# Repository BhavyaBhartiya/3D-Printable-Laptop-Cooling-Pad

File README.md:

# 3D Printable Laptop Cooling Pad

This is an open source laptop cooling pad designed to force air into the laptop like the Ilano V10 Cooling Pad. It uses 2 Arctic P12 Pro fans set in back portion of the cooling pad instead of th emiddle as most laptops have ducts at the back and not in the middle. It also uses a custom RP2040 based board to control the fan speed on the basis of the temperature of the CPU if in automatic mode or to set the fans to a constant speed if in manual mode. It requires a seperate 12v Power Input to run it without increasing load on the laptop by using the laptop to supply power to it. If it is to be  used in automatic mode then it should be connected to the laptop by a seperate cable so that the laptop can provide it with the CPU temperatures.

## Instructons for Using and Assembly

1. Attach the PCB to the area enclosed by 3 thin walls in between the fan. The PCB should slip in and sit snugly in the enclosure as it has been built to the exact dimensions for the pcb.

2. If you plan on using only manual mode then connect the 6 pin usb c receptacle to an external 12V Power Supply. The 6 pin USB C receptacle is the one on the right of the RP2040 chip.

3. If you wish to use automatic mode as well then attach a cable from any port of the computer to the 14 pin usb c receptacle present straight ahead of the RP2040 chip.

4. The OLED scrren will show current mode, fan speed and if any fan is facing any errors. If it is in automatic mode then it will also show the CPU temperature which will be updated once every 5 seconds.

5. You can use the Increase/ Decrease Buttons to increase or decrease the RPM of the fan by 500 in Manual Mode.

6. You can use the Mode Button to toggle the Mode of the Cooling Pad.

## Schematic

## PCB

## 3D-Design

## External Circuit

## BOM
| Designator                                            | Footprint                                       | Quantity | Value                         | LCSC Part # | Unit Price USD | Design Qty Cost USD | Link                                                                            |
|-------------------------------------------------------|-------------------------------------------------|----------|-------------------------------|-------------|----------------|---------------------|---------------------------------------------------------------------------------|
| C1, C19, C20                                          | 603                                             | 3        | 10uF                          | C96446      | 0.0557         | 0.1671              | https://www.lcsc.com/product-detail/C96446.html                                 |
| C2                                                    | 603                                             | 1        | 22uF                          | C2762594    | 0.1021         | 0.1021              | https://www.lcsc.com/product-detail/C2762594.html                               |
| C21, C24                                              | 402                                             | 2        | 1uF                           | C52923      | 0.0122         | 0.0244              | https://www.lcsc.com/product-detail/C52923.html                                 |
| C22, C23, C25, C26, C27, C28, C29, C30, C31, C32, C35 | 402                                             | 11       | 0.1uF                         | C1525       | 0.0046         | 0.0506              | https://www.lcsc.com/product-detail/C1525.html                                  |
| C33, C34                                              | 402                                             | 2        | 15pF                          | C86285      | 0.004          | 0.008               | https://www.lcsc.com/product-detail/C86285.html                                 |
| D1                                                    | D_SMB                                           | 1        | SMBJ15A                       | C83846      | 0.1183         | 0.1183              | https://www.lcsc.com/product-detail/C83846.html                                 |
| D2                                                    | D_SOD-123F                                      | 1        | BZT52H-A12                    | C7507853    | 0.1912         | 0.1912              | https://www.lcsc.com/product-detail/C7507853.html                               |
| D4                                                    | 603                                             | 1        | LED                           | C965804     | 0.0051         | 0.0051              | https://www.lcsc.com/product-detail/C965804.html                                |
| F1                                                    | 1812                                            | 1        | Littelfuse 1812L150/24MR      | C142805     | 0.0979         | 0.0979              | https://www.lcsc.com/product-detail/C142805.html                                |
| J1                                                    | TYPE-C-SMD_TYPE-C-6P-073                        | 1        | USB_C_Receptacle_PowerOnly_6P | C668623     | 0.0406         | 0.0406              | https://www.lcsc.com/product-detail/C668623.html                                |
| J10                                                   | PinHeader_1x02_P2.54mm_Vertical                 | 1        | DECREASE                      | C32713268   | 0.0154         | 0.0154              | https://www.lcsc.com/product-detail/C32713268.html                              |
| J11                                                   | USB_C_Receptacle_HRO_TYPE-C-31-M-12             | 1        | USB_C_Receptacle_USB2.0_14P   | C165948     | 0.1724         | 0.1724              | https://www.lcsc.com/product-detail/C165948.html                                |
| J13                                                   | PinHeader_1x03_P2.54mm_Vertical                 | 1        | Conn_01x03                    | C2937625    | 0.0198         | 0.0198              | https://www.lcsc.com/product-detail/C2937625.html                               |
| J5, J6                                                | PinHeader_1x04_P2.54mm_Vertical                 | 2        | Fan1_Connector                | C2691448    | 0.0275         | 0.055               | https://www.lcsc.com/product-detail/C2691448.html                               |
| J7                                                    | PinHeader_1x04_P2.54mm_Vertical                 | 1        | OLED                          | C2691448    | 0.0275         | 0.0275              | https://www.lcsc.com/product-detail/C2691448.html                               |
| J8                                                    | PinHeader_1x02_P2.54mm_Vertical                 | 1        | INCREASE                      | C32713268   | 0.0154         | 0.0154              | https://www.lcsc.com/product-detail/C32713268.html                              |
| J9                                                    | PinHeader_1x02_P2.54mm_Vertical                 | 1        | MODE                          | C32713268   | 0.0154         | 0.0154              | https://www.lcsc.com/product-detail/C32713268.html                              |
| L1                                                    | IND-SMD_L4.5-W4.1_SRP4020TA                     | 1        | SRP4020TA-2R2M                | C719179     | 0.6015         | 0.6015              | https://www.lcsc.com/product-detail/C719179.html                                |
| Q1                                                    | SOT-23                                          | 1        | DMP3099L                      | C2940610    | 0.0499         | 0.0499              | https://www.lcsc.com/product-detail/C2940610.html                               |
| Q2                                                    | SOT-23                                          | 1        | BSS138                        | C52895      | 0.0638         | 0.0638              | https://www.lcsc.com/product-detail/C52895.html                                 |
| R1, R12, R3                                           | 603                                             | 3        | 100K                          | C14675      | 0.0036         | 0.0108              | https://www.lcsc.com/product-detail/C14675.html                                 |
| R13, R16, R28, R34                                    | 402                                             | 4        | 10K                           | C60490      | 0.0033         | 0.0132              | https://www.lcsc.com/product-detail/C60490.html                                 |
| R14, R15, R20, R27, R29, R30, R33                     | 402                                             | 7        | 1k                            | C106235     | 0.0044         | 0.0308              | https://www.lcsc.com/product-detail/C106235.html                                |
| R21, R22, R23, R24                                    | 402                                             | 4        | 5.1K                          | C105872     | 0.003          | 0.012               | https://www.lcsc.com/product-detail/C105872.html                                |
| R25, R26                                              | 402                                             | 2        | 27                            | C138021     | 0.004          | 0.008               | https://www.lcsc.com/product-detail/C138021.html                                |
| R31, R32                                              | 402                                             | 2        | 4.7k                          | C105871     | 0.0038         | 0.0076              | https://www.lcsc.com/product-detail/C105871.html                                |
| SW1, SW2                                              | SW_Push_SPST_NO_Alps_SKRK                       | 2        | SW_Push                       | C720477     | 0.053          | 0.106               | https://www.lcsc.com/product-detail/C720477.html                                |
| U1                                                    | WSON-8-1EP_2x2mm_P0.5mm_EP0.9x1.6mm_ThermalVias | 1        | TPS62162DSG                   | C2863597    | 1.5159         | 1.5159              | https://www.lcsc.com/product-detail/C2863597.html                               |
| U2                                                    | SOT-23                                          | 1        | MCP1700x-330xxTT              | C39051      | 0.409          | 0.409               | https://www.lcsc.com/product-detail/C39051.html                                 |
| U5                                                    | Winbond_USON-8-1EP_3x2mm_P0.5mm_EP0.2x1.6mm     | 1        | W25Q16JVUXIQ TR               | C2843335    | 1.5882         | 1.5882              | https://www.lcsc.com/product-detail/C2843335.html                               |
| U6                                                    | QFN-56-1EP_7x7mm_P0.4mm_EP3.2x3.2mm             | 1        | RP2040                        | C2040       | 0.9968         | 0.9968              | https://www.lcsc.com/product-detail/C2040.html                                  |
| Y2                                                    | CRYSTAL-SMD_4P-L2.5-W2.0-BL-1                   | 1        | ABM8-272-T3                   | C20625731   | 0.62           | 0.62                | https://lcsc.com/product-detail/Crystals_Abracon-LLC-ABM8-272-T3_C20625731.html |
| Arctic P12 Pro                                        |                                                 | 2        |                               |             | 16.23          | 32.46               | https://www.arctic.de/en/P12-Pro/ACFAN00305A                                    |
| TOTAL                                                 |                                                 | 66       |                               |             |                | 39.6197             |                                                                                 |

### Credits - to KaiPereira for their excellent guide on [how to buid a custom devboard](https://github.com/KaiPereira/build-a-devboard)

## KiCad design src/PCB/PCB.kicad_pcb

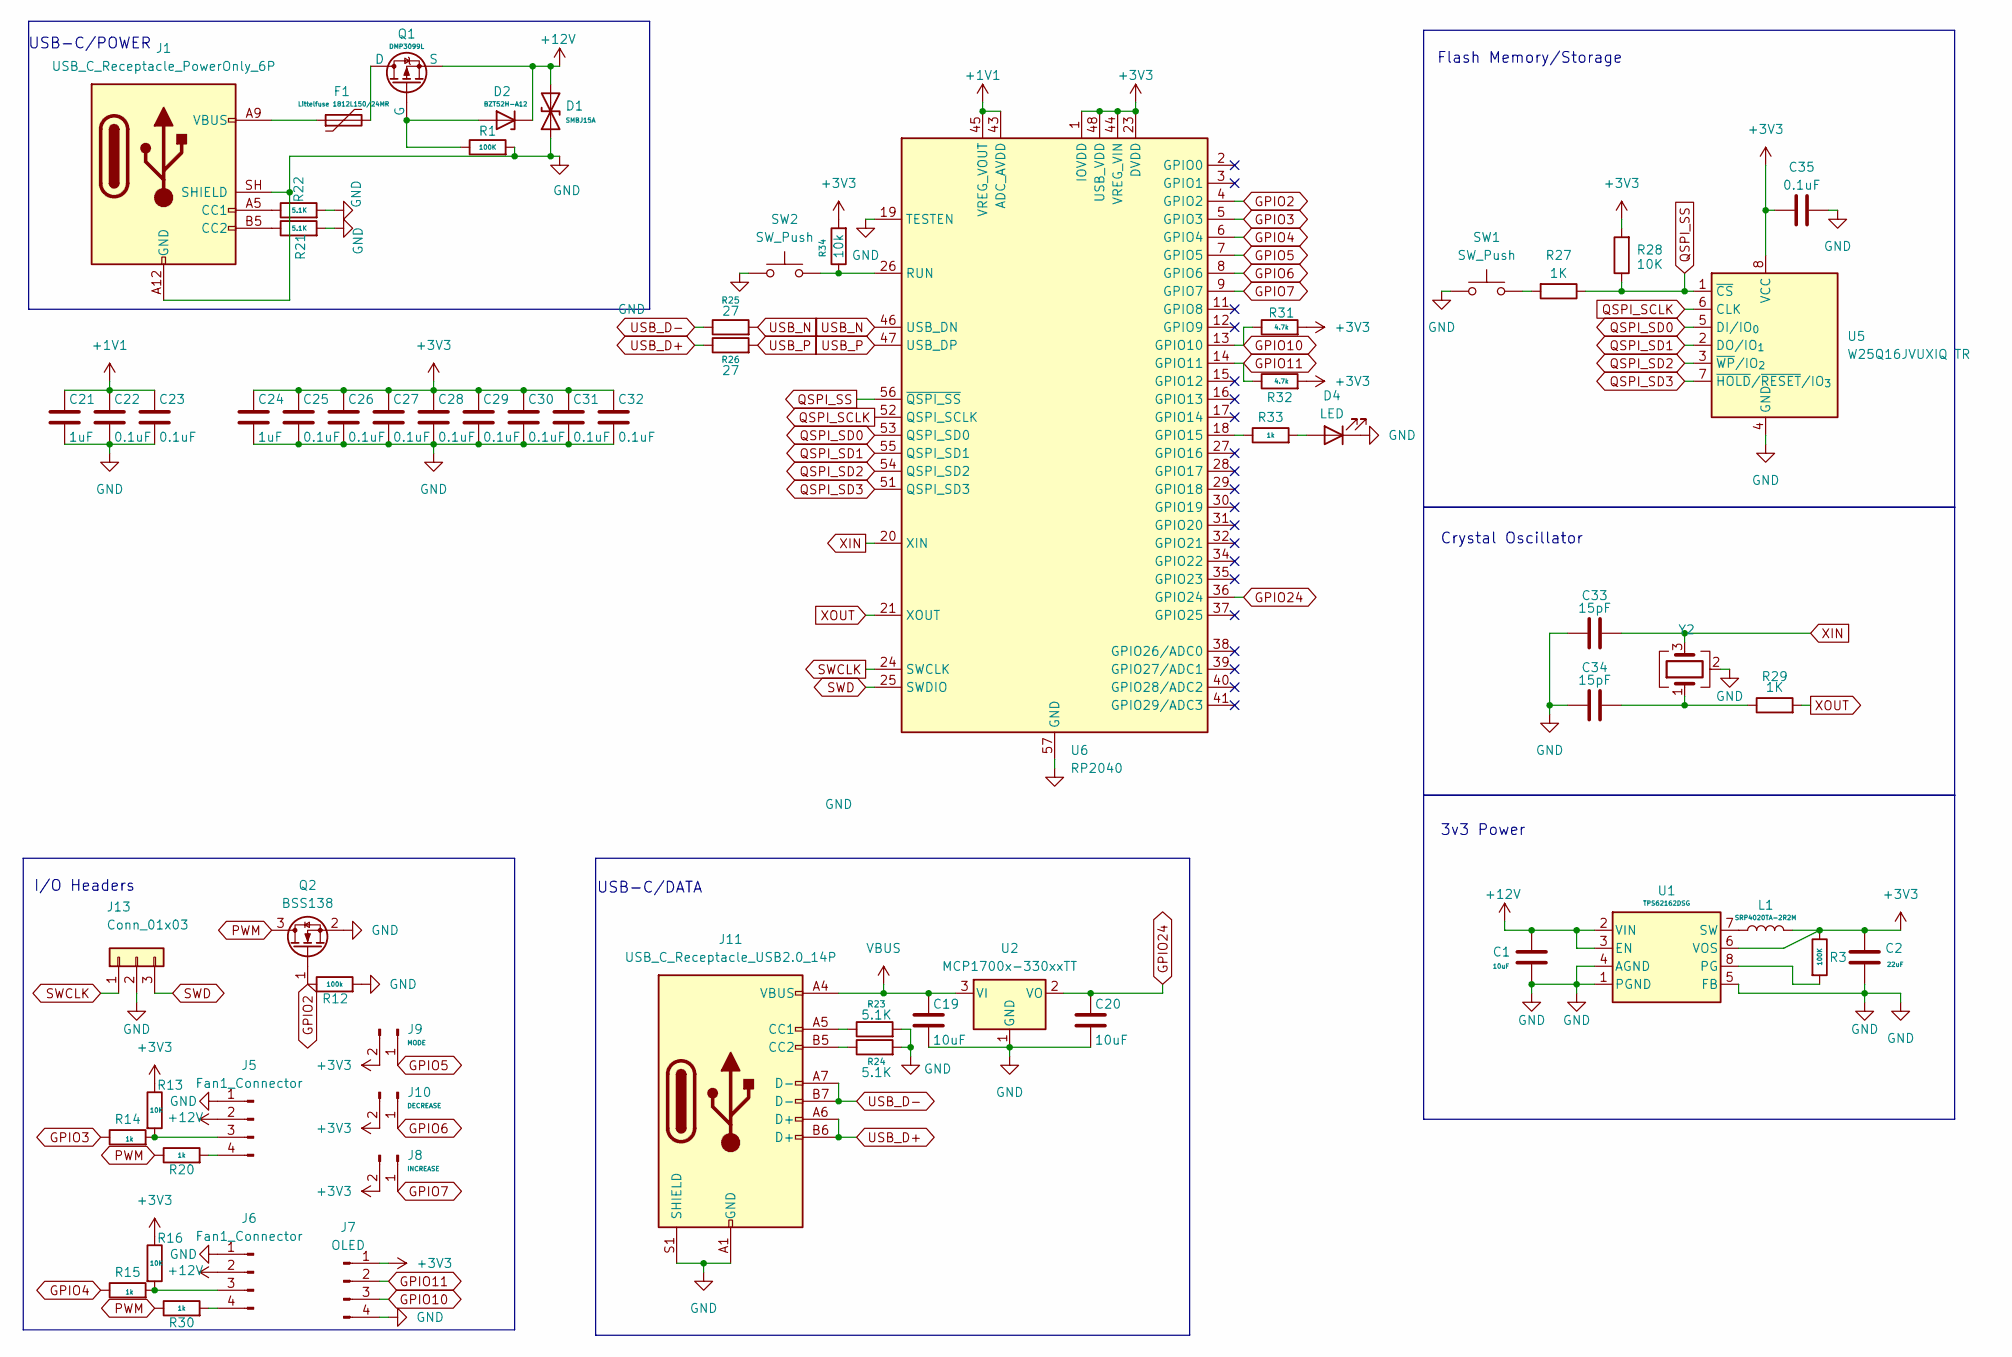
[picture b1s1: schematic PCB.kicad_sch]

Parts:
C1, C19, C20: 10uF; C_0603_1608Metric; LCSC Part Number C96446
C2: 22uF; C_0603_1608Metric; LCSC Part Number C2762594
C21, C24: 1uF; C_0402_1005Metric; LCSC Part Number C52923
C22, C23, C25, C26, C27, C28, C29, C30, C31, C32, C35: 0.1uF; C_0402_1005Metric; LCSC Part Number C1525
C33, C34: 15pF; C_0402_1005Metric; LCSC Part Number C86285
D1: SMBJ15A; D_SMB; LCSC Part Number C83846
D2: BZT52H-A12; D_SOD-123F; LCSC Part Number C7507853
D4: LED; LED_0603_1608Metric; LCSC Part Number C965804
F1: Littelfuse 1812L150/24MR; Fuse_1812_4532Metric; LCSC Part Number C142805
J1: USB_C_Receptacle_PowerOnly_6P; TYPE-C-SMD_TYPE-C-6P-073; LCSC Part Number TYPE-C 6P(073)
J5, J6: Fan1_Connector; PinHeader_1x04_P2.54mm_Vertical; LCSC Part Number C2691448
J7: OLED; PinHeader_1x04_P2.54mm_Vertical; LCSC Part Number C2691448
J8: INCREASE; PinHeader_1x02_P2.54mm_Vertical; LCSC Part Number C32713268
J9: MODE; PinHeader_1x02_P2.54mm_Vertical; LCSC Part Number C32713268
J10: DECREASE; PinHeader_1x02_P2.54mm_Vertical; LCSC Part Number C32713268
J11: USB_C_Receptacle_USB2.0_14P; USB_C_Receptacle_HRO_TYPE-C-31-M-12; LCSC Part Number C165948
J13: Conn_01x03; PinHeader_1x03_P2.54mm_Vertical; LCSC Part Number C2937625
L1: SRP4020TA-2R2M; IND-SMD_L4.5-W4.1_SRP4020TA; LCSC Part Number C719179
Q1: DMP3099L; SOT-23; LCSC Part Number C2940610
Q2: BSS138; SOT-23; LCSC Part Number C52895
R1, R3: 100K; R_0603_1608Metric; LCSC Part Number C14675
R12: 100k; R_0603_1608Metric; LCSC Part Number C14675
R13, R16, R28: 10K; R_0402_1005Metric; LCSC Part Number C60490
R14, R15, R20, R30, R33: 1k; R_0402_1005Metric; LCSC Part Number C106235
R21, R22, R23, R24: 5.1K; R_0402_1005Metric; LCSC Part Number C105872
R25, R26: 27; R_0402_1005Metric; LCSC Part Number C138021
R27, R29: 1K; R_0402_1005Metric; LCSC Part Number C106235
R31, R32: 4.7k; R_0402_1005Metric; LCSC Part Number C105871
R34: 10k; R_0402_1005Metric; LCSC Part Number C60490
SW1, SW2: SW_Push; SW_Push_SPST_NO_Alps_SKRK; LCSC Part Number C720477
U1: TPS62162DSG; WSON-8-1EP_2x2mm_P0.5mm_EP0.9x1.6mm_ThermalVias; LCSC Part Number C2863597
U2: MCP1700x-330xxTT; SOT-23; LCSC Part Number C39051
U5: W25Q16JVUXIQ TR; Winbond_USON-8-1EP_3x2mm_P0.5mm_EP0.2x1.6mm; LCSC Part Number C2843335
U6: RP2040; QFN-56-1EP_7x7mm_P0.4mm_EP3.2x3.2mm; LCSC Part Number C2040
Y2: ABM8-272-T3; CRYSTAL-SMD_4P-L2.5-W2.0-BL-1; LCSC Part Number C20625731

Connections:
+1V1: C21.1, C22.1, C23.1, U6.43 (ADC_AVDD), U6.45 (VREG_VOUT)
+3V3: C2.1, C24.1, C25.1, C26.1, C27.1, C28.1, C29.1, C30.1, C31.1, C32.1, C35.1, J7.1, J8.2, J9.2, J10.2, L1.2, R3.1, R13.1, R16.1, R28.2, R31.2, R32.2, R34.2, U1.6 (VOS), U5.8 (VCC), U6.1 (IOVDD), U6.10 (IOVDD), U6.22 (IOVDD), U6.23 (DVDD), U6.33 (IOVDD), U6.42 (IOVDD), U6.44 (VREG_VIN), U6.48 (USB_VDD), U6.49 (IOVDD), U6.50 (DVDD)
+12V: C1.1, D1.2 (A2), D2.1 (K), J5.2, J6.2, Q1.3 (S), U1.2 (VIN), U1.3 (EN)
GND: C1.2, C2.2, C19.2, C20.2, C21.2, C22.2, C23.2, C24.2, C25.2, C26.2, C27.2, C28.2, C29.2, C30.2, C31.2, C32.2, C33.1, C34.1, C35.2, D1.1 (A1), D4.1 (K), J1.A12 (GND), J1.B12 (GND), J1.SH (SHIELD), J5.1, J6.1, J7.4, J11.A1 (GND), J11.A12 (GND), J11.B1 (GND), J11.B12 (GND), J11.S1 (SHIELD), J13.2, Q2.2 (S), R1.2, R12.2, R21.2, R22.2, R23.2, R24.2, SW1.1, SW2.1, U1.1 (PGND), U1.4 (AGND), U1.5 (FB), U2.1 (GND), U5.4 (GND), U6.19 (TESTEN), U6.57 (GND), Y2.2 (G), Y2.4 (G)
GPIO2: Q2.1 (G), R12.1, U6.4 (GPIO2)
GPIO3: R14.1, U6.5 (GPIO3)
GPIO4: R15.1, U6.6 (GPIO4)
GPIO5: J9.1, U6.7 (GPIO5)
GPIO6: J10.1, U6.8 (GPIO6)
GPIO7: J8.1, U6.9 (GPIO7)
GPIO10: J7.3, R31.1, U6.13 (GPIO10)
GPIO11: J7.2, R32.1, U6.14 (GPIO11)
GPIO24: C20.1, U2.2 (VO), U6.36 (GPIO24)
unnamed: C34.2, R29.1, Y2.1
unnamed: D2.2 (A), Q1.2 (G), R1.1
unnamed: D4.2 (A), R33.2
unnamed: F1.1, J1.A9 (VBUS), J1.B9 (VBUS)
unnamed: J1.A5 (CC1), R21.1
unnamed: J1.B5 (CC2), R22.1
unnamed: J5.3, R13.2, R14.2
unnamed: J5.4, R20.2
unnamed: J6.3, R15.2, R16.2
unnamed: J6.4, R30.2
unnamed: J11.A5 (CC1), R23.1
unnamed: J11.B5 (CC2), R24.1
unnamed: F1.2, Q1.1 (D)
unnamed: R27.2, SW1.2
unnamed: R3.2, U1.8 (PG)
unnamed: L1.1, U1.7 (SW)
unnamed: R33.1, U6.18 (GPIO15)
unnamed: R34.1, SW2.2, U6.26 (RUN)
PWM: Q2.3 (D), R20.1, R30.1
QSPI_SCLK: U5.6 (CLK), U6.52 (QSPI_SCLK)
QSPI_SD0: U5.5 (DI/IO_{0}), U6.53 (QSPI_SD0)
QSPI_SD1: U5.2 (DO/IO_{1}), U6.55 (QSPI_SD1)
QSPI_SD2: U5.3 (~WP/IO_{2}), U6.54 (QSPI_SD2)
QSPI_SD3: U5.7 (~HOLD/~RESET/IO_{3}), U6.51 (QSPI_SD3)
QSPI_SS: R27.1, R28.1, U5.1 (~CS), U6.56 (~QSPI_SS)
SWCLK: J13.1, U6.24 (SWCLK)
SWD: J13.3, U6.25 (SWDIO)
USB_D+: J11.A6 (D+), J11.B6 (D+), R26.1
USB_D-: J11.A7 (D-), J11.B7 (D-), R25.1
USB_N: R25.2, U6.46 (USB_DN)
USB_P: R26.2, U6.47 (USB_DP)
VBUS: C19.1, J11.A4 (VBUS), J11.A9 (VBUS), J11.B4 (VBUS), J11.B9 (VBUS), U2.3 (VI)
XIN: C33.2, U6.20 (XIN), Y2.3
XOUT: R29.2, U6.21 (XOUT)

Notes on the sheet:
I/O Headers
USB-C/DATA
Crystal Oscillator
Flash Memory/Storage
USB-C/POWER
3v3 Power

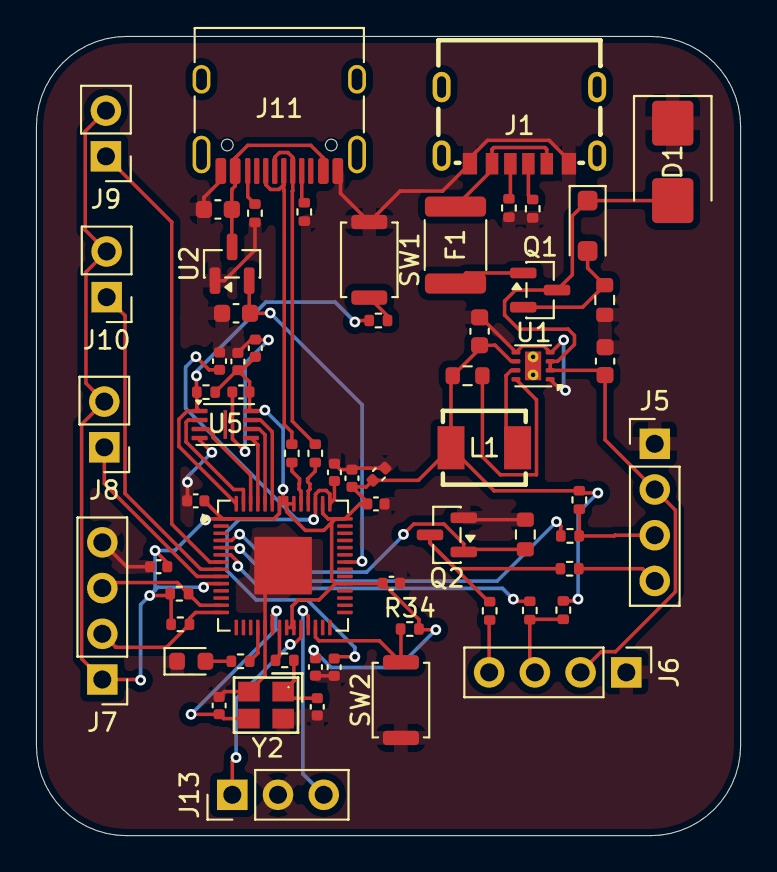
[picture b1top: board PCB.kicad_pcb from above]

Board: 2 copper layers, 39.1 x 44.4 mm, 64 parts (0 on the bottom side), 47 nets.

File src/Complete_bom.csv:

Designator,Footprint,Quantity,Value,LCSC Part #,Unit Price USD,Design Qty Cost USD,Link
"C1, C19, C20",603,3,10uF,C96446,0.0557,0.1671,https://www.lcsc.com/product-detail/C96446.html
C2,603,1,22uF,C2762594,0.1021,0.1021,https://www.lcsc.com/product-detail/C2762594.html
"C21, C24",402,2,1uF,C52923,0.0122,0.0244,https://www.lcsc.com/product-detail/C52923.html
"C22, C23, C25, C26, C27, C28, C29, C30, C31, C32, C35",402,11,0.1uF,C1525,0.0046,0.0506,https://www.lcsc.com/product-detail/C1525.html
"C33, C34",402,2,15pF,C86285,0.004,0.008,https://www.lcsc.com/product-detail/C86285.html
D1,D_SMB,1,SMBJ15A,C83846,0.1183,0.1183,https://www.lcsc.com/product-detail/C83846.html
D2,D_SOD-123F,1,BZT52H-A12,C7507853,0.1912,0.1912,https://www.lcsc.com/product-detail/C7507853.html
D4,603,1,LED,C965804,0.0051,0.0051,https://www.lcsc.com/product-detail/C965804.html
F1,1812,1,Littelfuse 1812L150/24MR,C142805,0.0979,0.0979,https://www.lcsc.com/product-detail/C142805.html
J1,TYPE-C-SMD_TYPE-C-6P-073,1,USB_C_Receptacle_PowerOnly_6P,C668623,0.0406,0.0406,https://www.lcsc.com/product-detail/C668623.html
J10,PinHeader_1x02_P2.54mm_Vertical,1,DECREASE,C32713268,0.0154,0.0154,https://www.lcsc.com/product-detail/C32713268.html
J11,USB_C_Receptacle_HRO_TYPE-C-31-M-12,1,USB_C_Receptacle_USB2.0_14P,C165948,0.1724,0.1724,https://www.lcsc.com/product-detail/C165948.html
J13,PinHeader_1x03_P2.54mm_Vertical,1,Conn_01x03,C2937625,0.0198,0.0198,https://www.lcsc.com/product-detail/C2937625.html
"J5, J6",PinHeader_1x04_P2.54mm_Vertical,2,Fan1_Connector,C2691448,0.0275,0.055,https://www.lcsc.com/product-detail/C2691448.html
J7,PinHeader_1x04_P2.54mm_Vertical,1,OLED,C2691448,0.0275,0.0275,https://www.lcsc.com/product-detail/C2691448.html
J8,PinHeader_1x02_P2.54mm_Vertical,1,INCREASE,C32713268,0.0154,0.0154,https://www.lcsc.com/product-detail/C32713268.html
J9,PinHeader_1x02_P2.54mm_Vertical,1,MODE,C32713268,0.0154,0.0154,https://www.lcsc.com/product-detail/C32713268.html
L1,IND-SMD_L4.5-W4.1_SRP4020TA,1,SRP4020TA-2R2M,C719179,0.6015,0.6015,https://www.lcsc.com/product-detail/C719179.html
Q1,SOT-23,1,DMP3099L,C2940610,0.0499,0.0499,https://www.lcsc.com/product-detail/C2940610.html
Q2,SOT-23,1,BSS138,C52895,0.0638,0.0638,https://www.lcsc.com/product-detail/C52895.html
"R1, R12, R3",603,3,100K,C14675,0.0036,0.0108,https://www.lcsc.com/product-detail/C14675.html
"R13, R16, R28, R34",402,4,10K,C60490,0.0033,0.0132,https://www.lcsc.com/product-detail/C60490.html
"R14, R15, R20, R27, R29, R30, R33",402,7,1k,C106235,0.0044,0.0308,https://www.lcsc.com/product-detail/C106235.html
"R21, R22, R23, R24",402,4,5.1K,C105872,0.003,0.012,https://www.lcsc.com/product-detail/C105872.html
"R25, R26",402,2,27,C138021,0.004,0.008,https://www.lcsc.com/product-detail/C138021.html
"R31, R32",402,2,4.7k,C105871,0.0038,0.0076,https://www.lcsc.com/product-detail/C105871.html
"SW1, SW2",SW_Push_SPST_NO_Alps_SKRK,2,SW_Push,C720477,0.053,0.106,https://www.lcsc.com/product-detail/C720477.html
U1,WSON-8-1EP_2x2mm_P0.5mm_EP0.9x1.6mm_ThermalVias,1,TPS62162DSG,C2863597,1.5159,1.5159,https://www.lcsc.com/product-detail/C2863597.html
U2,SOT-23,1,MCP1700x-330xxTT,C39051,0.409,0.409,https://www.lcsc.com/product-detail/C39051.html
U5,Winbond_USON-8-1EP_3x2mm_P0.5mm_EP0.2x1.6mm,1,W25Q16JVUXIQ TR,C2843335,1.5882,1.5882,https://www.lcsc.com/product-detail/C2843335.html
U6,QFN-56-1EP_7x7mm_P0.4mm_EP3.2x3.2mm,1,RP2040,C2040,0.9968,0.9968,https://www.lcsc.com/product-detail/C2040.html
Y2,CRYSTAL-SMD_4P-L2.5-W2.0-BL-1,1,ABM8-272-T3,C20625731 ,0.62,0.62,https://lcsc.com/product-detail/Crystals_Abracon-LLC-ABM8-27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
Arctic P12 Pro,,2,,,16.23,32.46,https://www.arctic.de/en/P12-Pro/ACFAN00305A
TOTAL,,66,,,,39.6197,
